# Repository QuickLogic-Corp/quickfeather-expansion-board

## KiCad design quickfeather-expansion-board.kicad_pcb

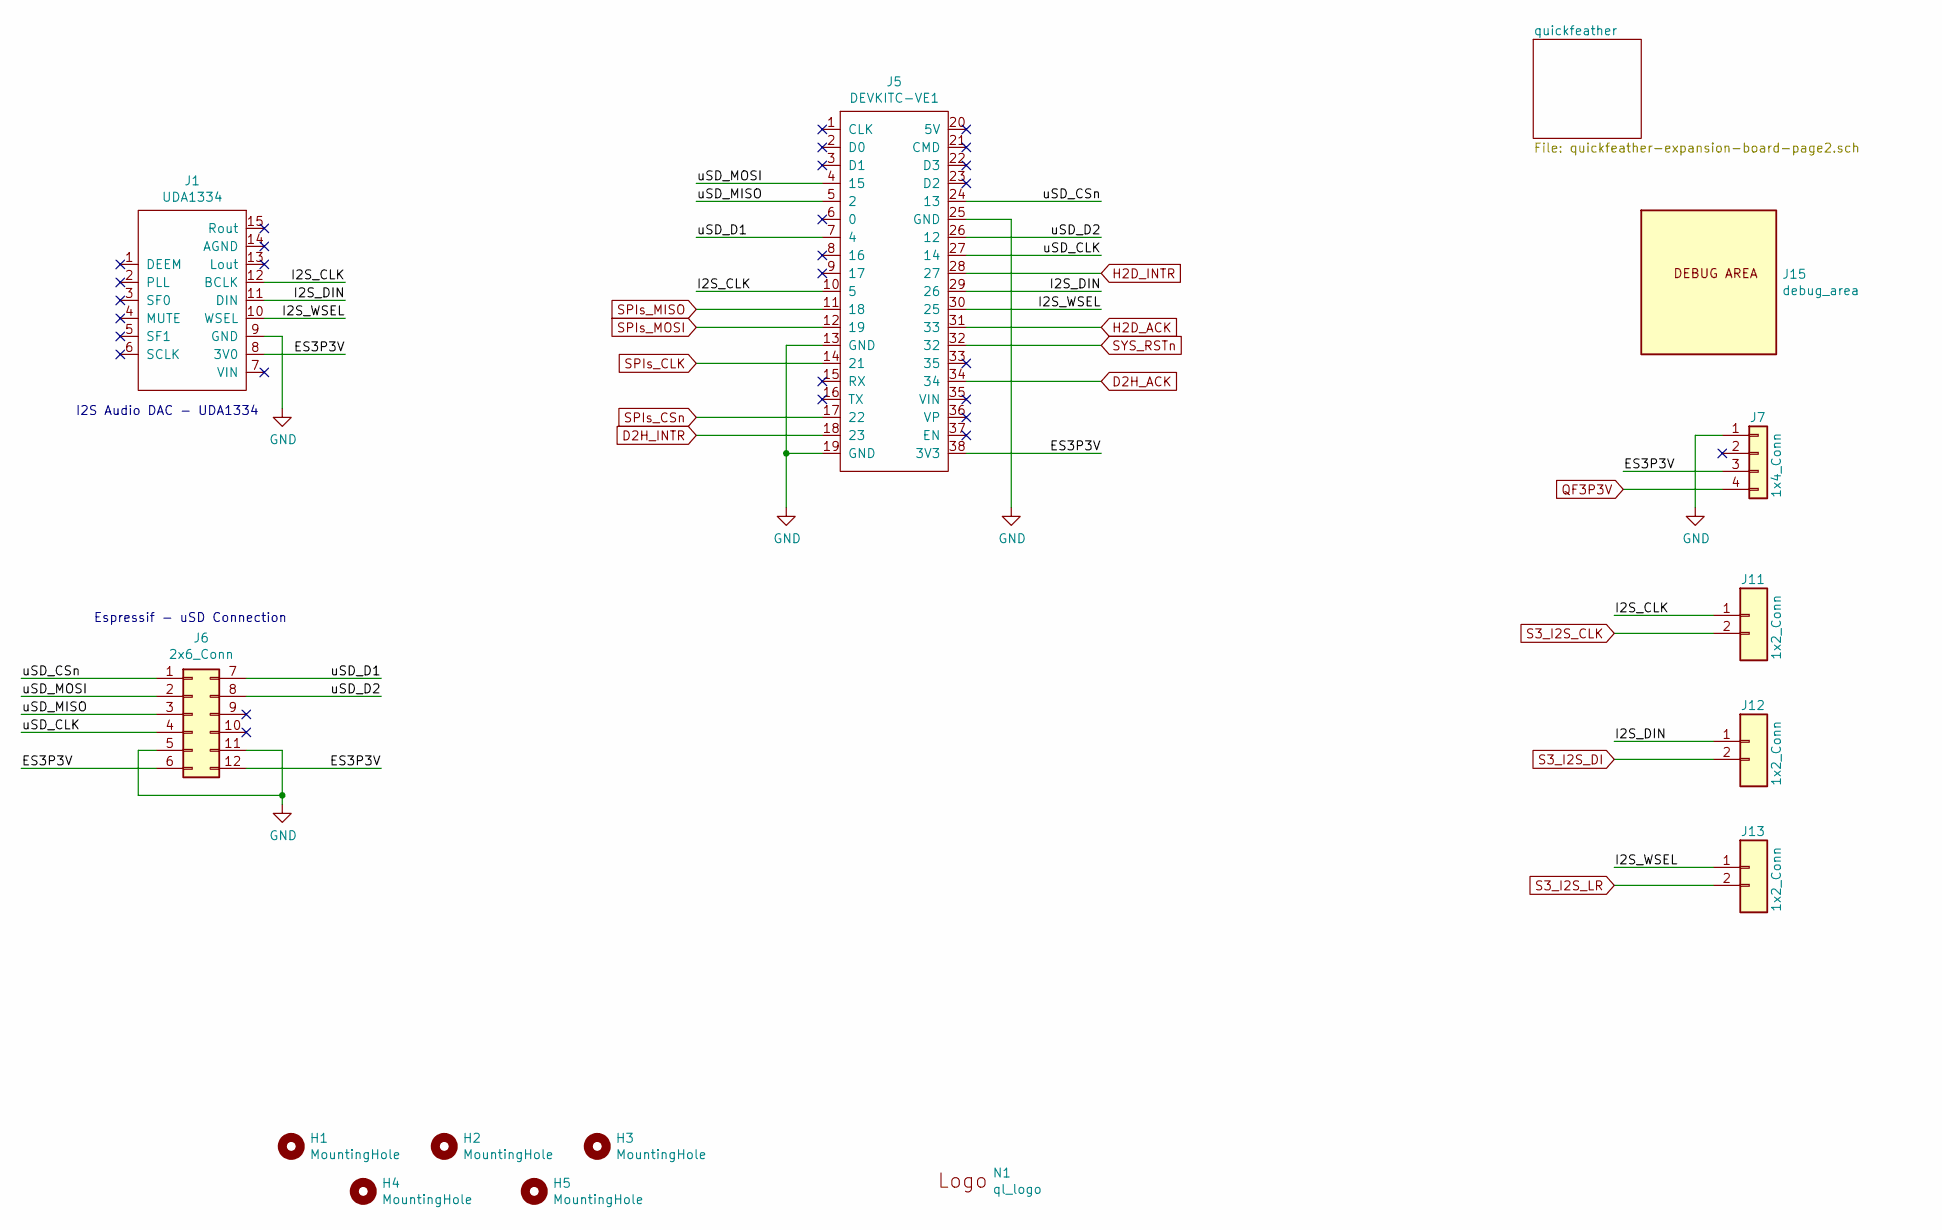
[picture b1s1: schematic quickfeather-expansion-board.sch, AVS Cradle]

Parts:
H1, H2, H3, H4, H5: MountingHole; MPAD
J1: UDA1334; uda1334
J5: DEVKITC-VE1; devkitc
J6: 2x6_Conn
J7: 1x4_Conn
J11, J12, J13: 1x2_Conn
J15: debug_area
N1: ql_logo; Ql_logo

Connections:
/ES3P3V: J1.8 (3V0), J5.38 (3V3), J6.6, J6.12, J7.3
/I2S_CLK: J1.12 (BCLK), J5.10 (5), J11.1
/I2S_DIN: J1.11 (DIN), J5.29 (26), J12.1
/I2S_WSEL: J1.10 (WSEL), J5.30 (25), J13.1
/uSD_CLK: J5.27 (14), J6.4
/uSD_CSn: J5.24 (13), J6.1
/uSD_D1: J5.7 (4), J6.7
/uSD_D2: J5.26 (12), J6.8
/uSD_MISO: J5.5 (2), J6.3
/uSD_MOSI: J5.4 (15), J6.2
D2H_ACK: J5.34; also elsewhere on the board
D2H_INTR: J5.18 (23); also elsewhere on the board
GND: J1.9 (GND), J5.13 (GND), J5.19 (GND), J5.25 (GND), J6.5, J6.11, J7.1; also elsewhere on the board
H2D_ACK: J5.31 (33); also elsewhere on the board
H2D_INTR: J5.28 (27); also elsewhere on the board
QF3P3V: J7.4; also elsewhere on the board
S3_I2S_CLK: J11.2; also elsewhere on the board
S3_I2S_DI: J12.2; also elsewhere on the board
S3_I2S_LR: J13.2; also elsewhere on the board
SPIs_CLK: J5.14 (21); also elsewhere on the board
SPIs_CSn: J5.17 (22); also elsewhere on the board
SPIs_MISO: J5.11 (18); also elsewhere on the board
SPIs_MOSI: J5.12 (19); also elsewhere on the board
SYS_RSTn: J5.32; also elsewhere on the board

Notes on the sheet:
I2S Audio DAC - UDA1334
Espressif - uSD Connection

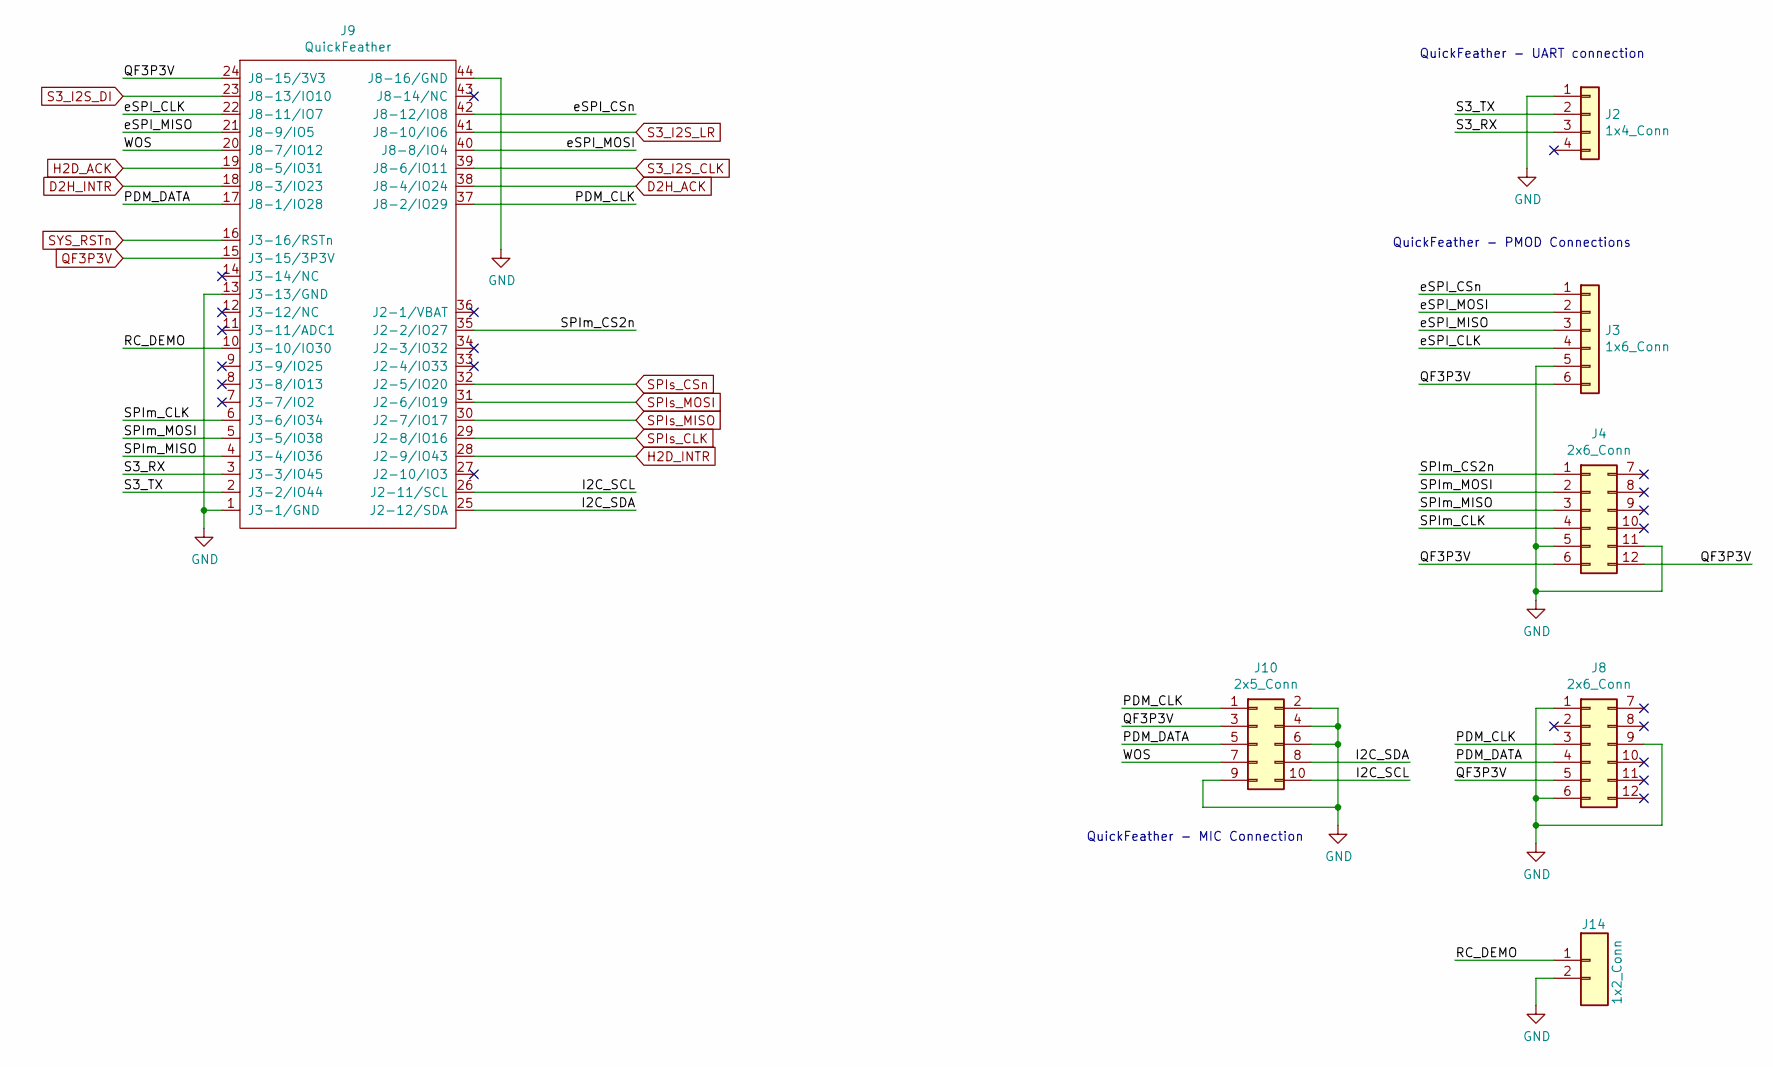
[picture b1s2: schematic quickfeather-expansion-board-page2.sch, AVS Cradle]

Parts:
J2: 1x4_Conn
J3: 1x6_Conn
J4, J8: 2x6_Conn
J9: QuickFeather; quickfeather
J10: 2x5_Conn
J14: 1x2_Conn

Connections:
/quickfeather/I2C_SCL: J9.26 (J2-11/SCL), J10.10
/quickfeather/I2C_SDA: J9.25 (J2-12/SDA), J10.8
/quickfeather/PDM_CLK: J8.3, J9.37 (J8-2/IO29), J10.1
/quickfeather/PDM_DATA: J8.4, J9.17 (J8-1/IO28), J10.5
/quickfeather/RC_DEMO: J9.10 (J3-10/IO30), J14.1
/quickfeather/S3_RX: J2.3, J9.3 (J3-3/IO45)
/quickfeather/S3_TX: J2.2, J9.2 (J3-2/IO44)
/quickfeather/SPIm_CLK: J4.4, J9.6 (J3-6/IO34)
/quickfeather/SPIm_CS2n: J4.1, J9.35 (J2-2/IO27)
/quickfeather/SPIm_MISO: J4.3, J9.4 (J3-4/IO36)
/quickfeather/SPIm_MOSI: J4.2, J9.5 (J3-5/IO38)
/quickfeather/WOS: J9.20 (J8-7/IO12), J10.7
/quickfeather/eSPI_CLK: J3.4, J9.22 (J8-11/IO7)
/quickfeather/eSPI_CSn: J3.1, J9.42 (J8-12/IO8)
/quickfeather/eSPI_MISO: J3.3, J9.21 (J8-9/IO5)
/quickfeather/eSPI_MOSI: J3.2, J9.40 (J8-8/IO4)
D2H_ACK: J9.38 (J8-4/IO24); also elsewhere on the board
D2H_INTR: J9.18 (J8-3/IO23); also elsewhere on the board
GND: J2.1, J3.5, J4.5, J4.11, J8.1, J8.6, J8.9, J9.1 (J3-1/GND), J9.13 (J3-13/GND), J9.44 (J8-16/GND), J10.2, J10.4, J10.6, J10.9, J14.2; also elsewhere on the board
H2D_ACK: J9.19 (J8-5/IO31); also elsewhere on the board
H2D_INTR: J9.28 (J2-9/IO43); also elsewhere on the board
QF3P3V: J3.6, J4.6, J4.12, J8.5, J9.15 (J3-15/3P3V), J9.24 (J8-15/3V3), J10.3; also elsewhere on the board
S3_I2S_CLK: J9.39 (J8-6/IO11); also elsewhere on the board
S3_I2S_DI: J9.23 (J8-13/IO10); also elsewhere on the board
S3_I2S_LR: J9.41 (J8-10/IO6); also elsewhere on the board
SPIs_CLK: J9.29 (J2-8/IO16); also elsewhere on the board
SPIs_CSn: J9.32 (J2-5/IO20); also elsewhere on the board
SPIs_MISO: J9.30 (J2-7/IO17); also elsewhere on the board
SPIs_MOSI: J9.31 (J2-6/IO19); also elsewhere on the board
SYS_RSTn: J9.16 (J3-16/RSTn); also elsewhere on the board

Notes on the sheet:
QuickFeather - UART connection
QuickFeather - PMOD Connections
QuickFeather - MIC Connection

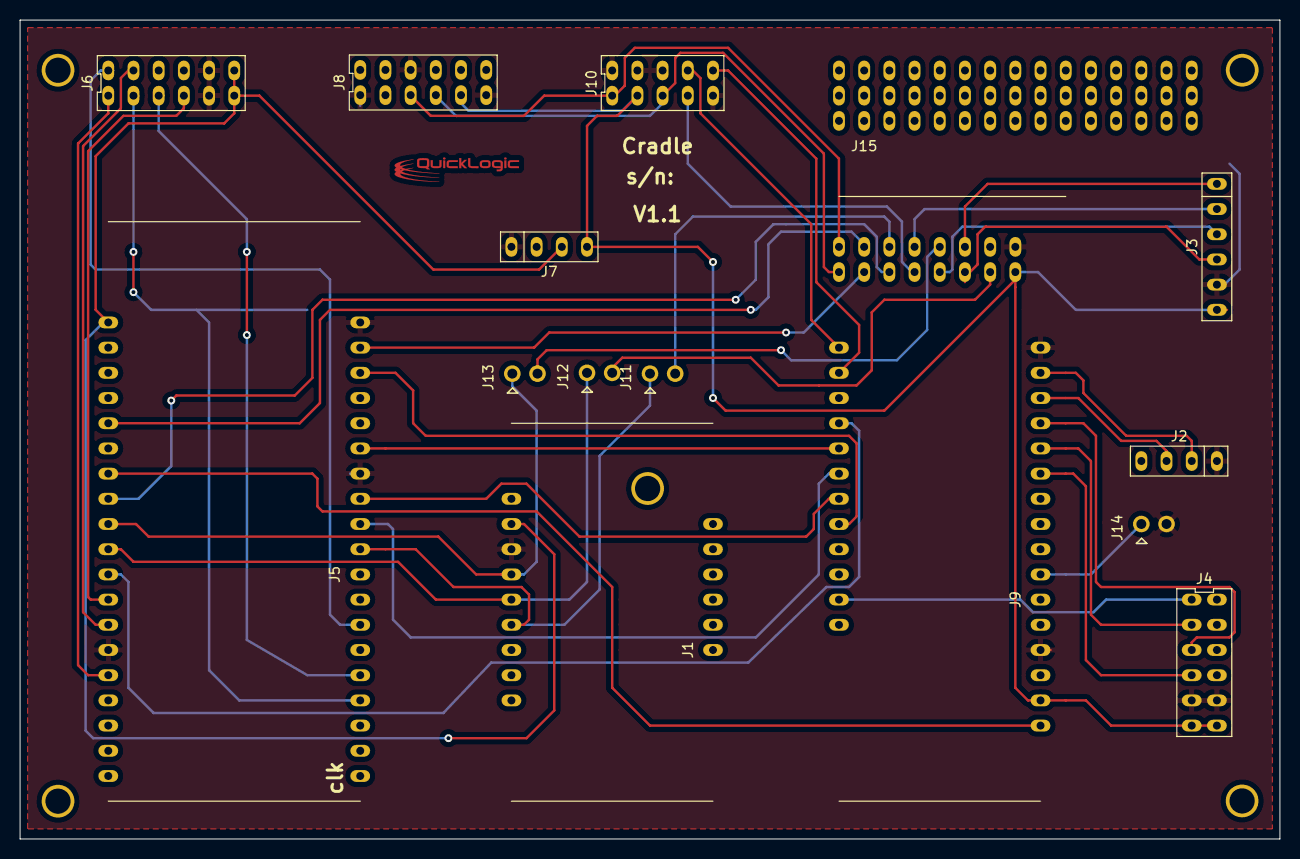
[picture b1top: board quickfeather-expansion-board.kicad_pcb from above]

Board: 2 copper layers, 127.0 x 82.6 mm, 21 parts (0 on the bottom side), 40 nets.

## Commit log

2020-11-02 Submit QuickFeather Expansion Board: AVS Cradle
